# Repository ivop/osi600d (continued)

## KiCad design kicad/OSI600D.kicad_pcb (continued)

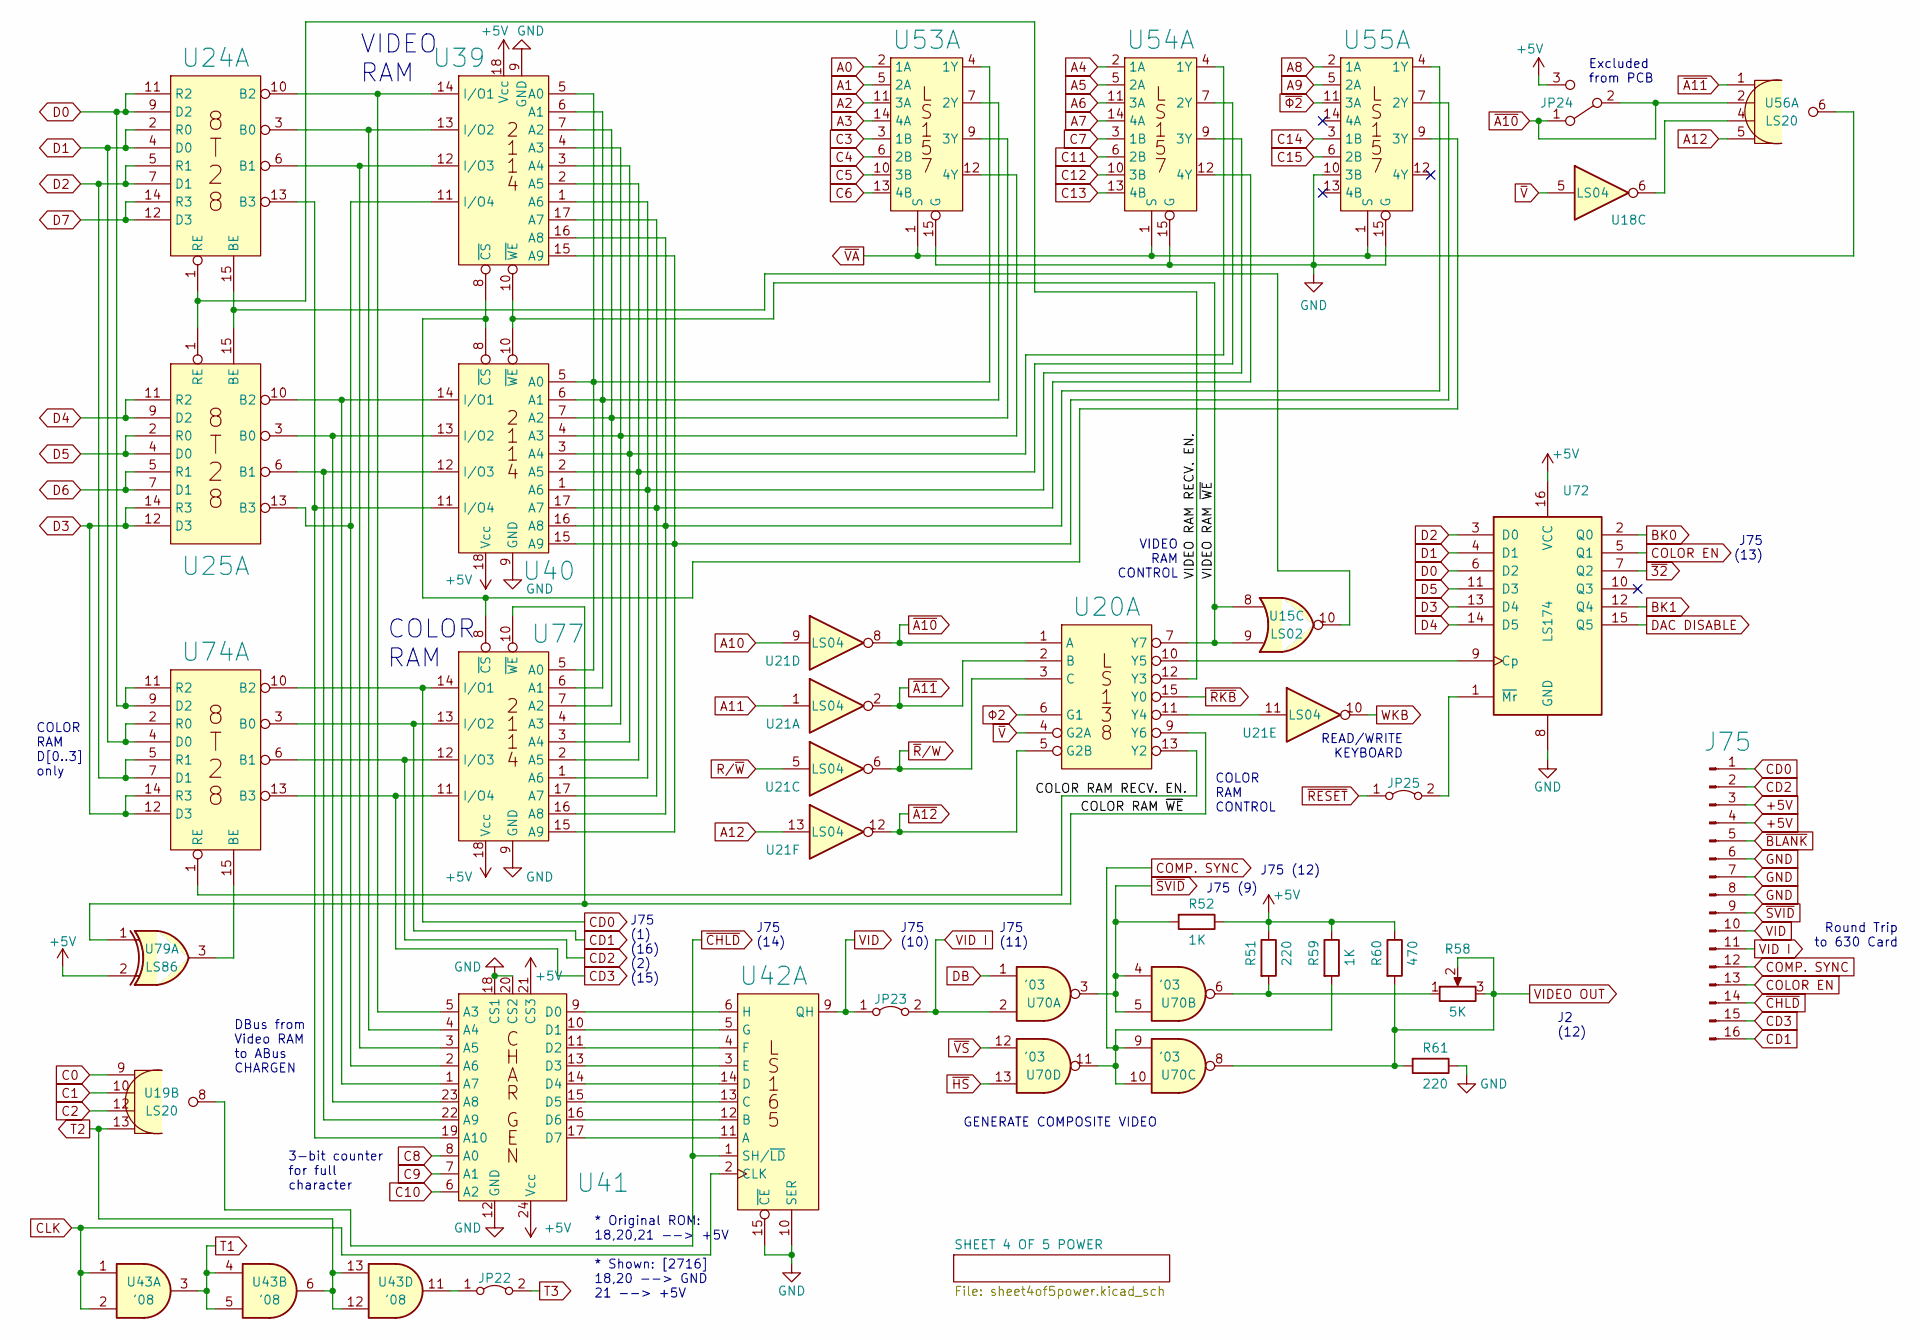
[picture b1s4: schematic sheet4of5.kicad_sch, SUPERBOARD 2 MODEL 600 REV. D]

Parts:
J75: Conn_01x16_Male; DIP-16_W7.62mm_Socket_LongPads
JP22, JP23, JP25: Jumper_2_Bridged; Closed_PinHeader_1x02_P2.54mm_Vertical
JP24: JUMPER; PinHeader_1x03_P2.54mm_Vertical
R51, R61: 220; R_Axial_DIN0207_L6.3mm_D2.5mm_P2.54mm_Vertical
R52, R59: 1K; R_Axial_DIN0207_L6.3mm_D2.5mm_P2.54mm_Vertical
R58: 5K; Potentiometer_Bourns_3296W_Vertical
R60: 470; R_Axial_DIN0207_L6.3mm_D2.5mm_P2.54mm_Vertical
U15: LS02; DIP-14_W7.62mm_Socket_LongPads
U18, U21: LS04; DIP-14_W7.62mm_Socket_LongPads
U19, U56: LS20; DIP-14_W7.62mm_Socket_LongPads
U20: LS138; DIP-16_W7.62mm_Socket_LongPads
U24, U25, U74: 8T28; DIP-16_W7.62mm_Socket_LongPads
U39: 2114 CS BOTTOM COMPACT; DIP-18_W7.62mm_Socket_LongPads
U40, U77: 2114 CS TOP COMPACT; DIP-18_W7.62mm_Socket_LongPads
U41: CHARGEN; DIP-24_W15.24mm_Socket_LongPads
U42: LS165; DIP-16_W7.62mm_Socket_LongPads
U43: '08; DIP-14_W7.62mm_Socket_LongPads
U53, U54, U55: LS157; DIP-16_W7.62mm_Socket_LongPads
U70: '03; DIP-14_W7.62mm_Socket_LongPads
U72: LS174; DIP-16_W7.62mm_Socket_LongPads
U79: LS86; DIP-14_W7.62mm_Socket_LongPads

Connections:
+5V: J75.3, J75.4, JP24.3, R51.1, R52.1, R59.1, R60.1, U39.18 (Vcc), U40.18 (Vcc), U41.21 (CS3), U41.24 (Vcc), U72.16 (VCC), U77.18 (Vcc), U79.2; also elsewhere on the board
/SHEET 4 OF 5/COLOR RAM RECV. EN.: U20.13 (Y2), U74.1 (RE)
/SHEET 4 OF 5/COLOR RAM ~WE: U20.9 (Y6), U77.10 (~WE), U79.1
/SHEET 4 OF 5/VIDEO RAM RECV. EN.: U20.12 (Y3), U24.1 (RE), U25.1 (RE)
/SHEET 4 OF 5/VIDEO RAM ~WE: U15.8, U15.9, U20.7 (Y7), U39.10 (~WE), U40.10 (~WE)
A0: U53.2 (1A); also elsewhere on the board
A1: U53.5 (2A); also elsewhere on the board
A2: U53.11 (3A); also elsewhere on the board
A3: U53.14 (4A); also elsewhere on the board
A4: U54.2 (1A); also elsewhere on the board
A5: U54.5 (2A); also elsewhere on the board
A6: U54.11 (3A); also elsewhere on the board
A7: U54.14 (4A); also elsewhere on the board
A8: U55.2 (1A); also elsewhere on the board
A9: U55.5 (2A); also elsewhere on the board
A10: U21.9; also elsewhere on the board
A11: U21.1; also elsewhere on the board
A12: U21.13, U56.5 (1D); also elsewhere on the board
BK0: U72.2 (Q0); also elsewhere on the board
BK1: U72.12 (Q4); also elsewhere on the board
C0: U19.9 (2A); also elsewhere on the board
C1: U19.10 (2B); also elsewhere on the board
C2: U19.12 (2C); also elsewhere on the board
C3: U53.3 (1B); also elsewhere on the board
C4: U53.6 (2B); also elsewhere on the board
C5: U53.10 (3B); also elsewhere on the board
C6: U53.13 (4B); also elsewhere on the board
C7: U54.3 (1B); also elsewhere on the board
C8: U41.8 (A0); also elsewhere on the board
C9: U41.7 (A1); also elsewhere on the board
C10: U41.6 (A2); also elsewhere on the board
C11: U54.6 (2B); also elsewhere on the board
C12: U54.10 (3B); also elsewhere on the board
C13: U54.13 (4B); also elsewhere on the board
C14: U55.3 (1B); also elsewhere on the board
C15: U55.6 (2B); also elsewhere on the board
CD0: J75.1, U74.10 (B2), U77.14 (I/O1)
CD1: J75.16, U74.3 (B0), U77.13 (I/O2)
CD2: J75.2, U74.6 (B1), U77.12 (I/O3)
CD3: J75.15, U74.13 (B3), U77.11 (I/O4)
CLK: U42.2 (CLK), U43.1, U43.2; also elsewhere on the board
COLOR EN: J75.13, U72.5 (Q1)
COMP. SYNC: J75.12, R59.2, U70.9, U70.10, U70.11
D0: U24.9 (D2), U24.11 (R2), U72.6 (D2), U74.9 (D2), U74.11 (R2); also elsewhere on the board
D1: U24.2 (R0), U24.4 (D0), U72.4 (D1), U74.2 (R0), U74.4 (D0); also elsewhere on the board
D2: U24.5 (R1), U24.7 (D1), U72.3 (D0), U74.5 (R1), U74.7 (D1); also elsewhere on the board
D3: U25.12 (D3), U25.14 (R3), U72.13 (D4), U74.12 (D3), U74.14 (R3); also elsewhere on the board
D4: U25.9 (D2), U25.11 (R2), U72.14 (D5); also elsewhere on the board
D5: U25.2 (R0), U25.4 (D0), U72.11 (D3); also elsewhere on the board
D6: U25.5 (R1), U25.7 (D1); also elsewhere on the board
D7: U24.12 (D3), U24.14 (R3); also elsewhere on the board
DAC DISABLE: U72.15 (Q5); also elsewhere on the board
DB: U70.1; also elsewhere on the board
GND: J75.6, J75.7, J75.8, R61.1, U39.9 (GND), U40.9 (GND), U41.12 (GND), U41.18 (CS1), U41.20 (CS2), U42.10 (SER), U42.15 (~CE), U53.15 (G), U54.15 (G), U55.10 (3B), U55.15 (G), U72.8 (GND), U77.9 (GND); also elsewhere on the board
unnamed: JP22.1 (A), U43.11
unnamed: JP25.2 (B), U72.1 (~Mr)
unnamed: R51.2, R58.1, U70.6
unnamed: U15.10, U24.15 (BE), U25.15 (BE)
unnamed: U18.6, U56.4 (1C)
unnamed: U20.10 (Y5), U72.9 (Cp)
unnamed: U20.11 (Y4), U21.11
unnamed: U24.3 (B0), U39.13 (I/O2), U41.4 (A4)
unnamed: U24.6 (B1), U39.12 (I/O3), U41.3 (A5)
unnamed: U24.10 (B2), U39.14 (I/O1), U41.5 (A3)
unnamed: U24.13 (B3), U40.11 (I/O4), U41.19 (A10)
unnamed: U25.3 (B0), U40.13 (I/O2), U41.23 (A8)
unnamed: U25.6 (B1), U40.12 (I/O3), U41.22 (A9)
unnamed: U25.10 (B2), U40.14 (I/O1), U41.1 (A7)
unnamed: U25.13 (B3), U39.11 (I/O4), U41.2 (A6)
unnamed: U39.1 (A6), U40.1 (A6), U54.9 (3Y), U77.1 (A6)
unnamed: U39.2 (A5), U40.2 (A5), U54.7 (2Y), U77.2 (A5)
unnamed: U39.3 (A4), U40.3 (A4), U54.4 (1Y), U77.3 (A4)
unnamed: U39.4 (A3), U40.4 (A3), U53.12 (4Y), U77.4 (A3)
unnamed: U39.5 (A0), U40.5 (A0), U53.4 (1Y), U77.5 (A0)
unnamed: U39.6 (A1), U40.6 (A1), U53.7 (2Y), U77.6 (A1)
unnamed: U39.7 (A2), U40.7 (A2), U53.9 (3Y), U77.7 (A2)
unnamed: U39.8 (~CS), U40.8 (~CS), U55.9 (3Y), U77.8 (~CS)
unnamed: U39.15 (A9), U40.15 (A9), U55.7 (2Y), U77.15 (A9)
unnamed: U39.16 (A8), U40.16 (A8), U55.4 (1Y), U77.16 (A8)
unnamed: U39.17 (A7), U40.17 (A7), U54.12 (4Y), U77.17 (A7)
unnamed: U41.9 (D0), U42.6 (H)
unnamed: U41.10 (D1), U42.5 (G)
unnamed: U41.11 (D2), U42.4 (F)
unnamed: U41.13 (D3), U42.3 (E)
unnamed: U41.14 (D4), U42.14 (D)
unnamed: U41.15 (D5), U42.13 (C)
unnamed: U41.16 (D6), U42.12 (B)
unnamed: U41.17 (D7), U42.11 (A)
unnamed: U74.15 (BE), U79.3
R/~W: U21.5; also elsewhere on the board
T1: U43.3, U43.4, U43.5
T2: U19.13 (2D), U43.6, U43.12, U43.13
T3: JP22.2 (B); also elsewhere on the board
VID: J75.10, JP23.1 (A), U42.9 (QH)
VID I: J75.11, JP23.2 (B), U70.2
VIDEO OUT: R58.2, R58.3, R60.2, R61.2, U70.8; also elsewhere on the board
WKB: U21.10; also elsewhere on the board
~32: U72.7 (Q2); also elsewhere on the board
~A10: JP24.1, JP24.2, U20.1 (A), U21.8, U56.2 (1B); also elsewhere on the board
~A11: U20.2 (B), U21.2, U56.1 (1A); also elsewhere on the board
~A12: U20.5 (G2B), U21.12; also elsewhere on the board
~BLANK: J75.5; also elsewhere on the board
~CHLD: J75.14, U19.8 (2Y), U42.1 (SH/~LD)
~HS: U70.13; also elsewhere on the board
~RESET: JP25.1 (A); also elsewhere on the board
~RKB: U20.15 (Y0); also elsewhere on the board
~R/W: U20.3 (C), U21.6; also elsewhere on the board
~SVID: J75.9, R52.2, U70.3, U70.4, U70.5
~VA: U53.1 (S), U54.1 (S), U55.1 (S), U56.6 (1Y); also elsewhere on the board
~VS: U70.12; also elsewhere on the board
~V: U18.5, U20.4 (G2A); also elsewhere on the board
~Φ2: U55.11 (3A); also elsewhere on the board
Φ2: U20.6 (G1); also elsewhere on the board

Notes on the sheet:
VIDEO RAM
Excluded from PCB
COLOR RAM
* Original ROM: 18,20,21 --> +5V * Shown: [2716] 18,20 --> GND 21 --> +5V
J75 (10)
READ/WRITE KEYBOARD
J75 (9)
J75 (14)
J2 (12)
GENERATE COMPOSITE VIDEO
J75 (13)
J75 (11)
3-bit counter for full character
J75 (1) (16) (2) (15)
Round Trip to 630 Card
COLOR RAM D[0..3] only
VIDEO RAM CONTROL
J75 (12)
DBus from Video RAM to ABus CHARGEN
COLOR RAM CONTROL

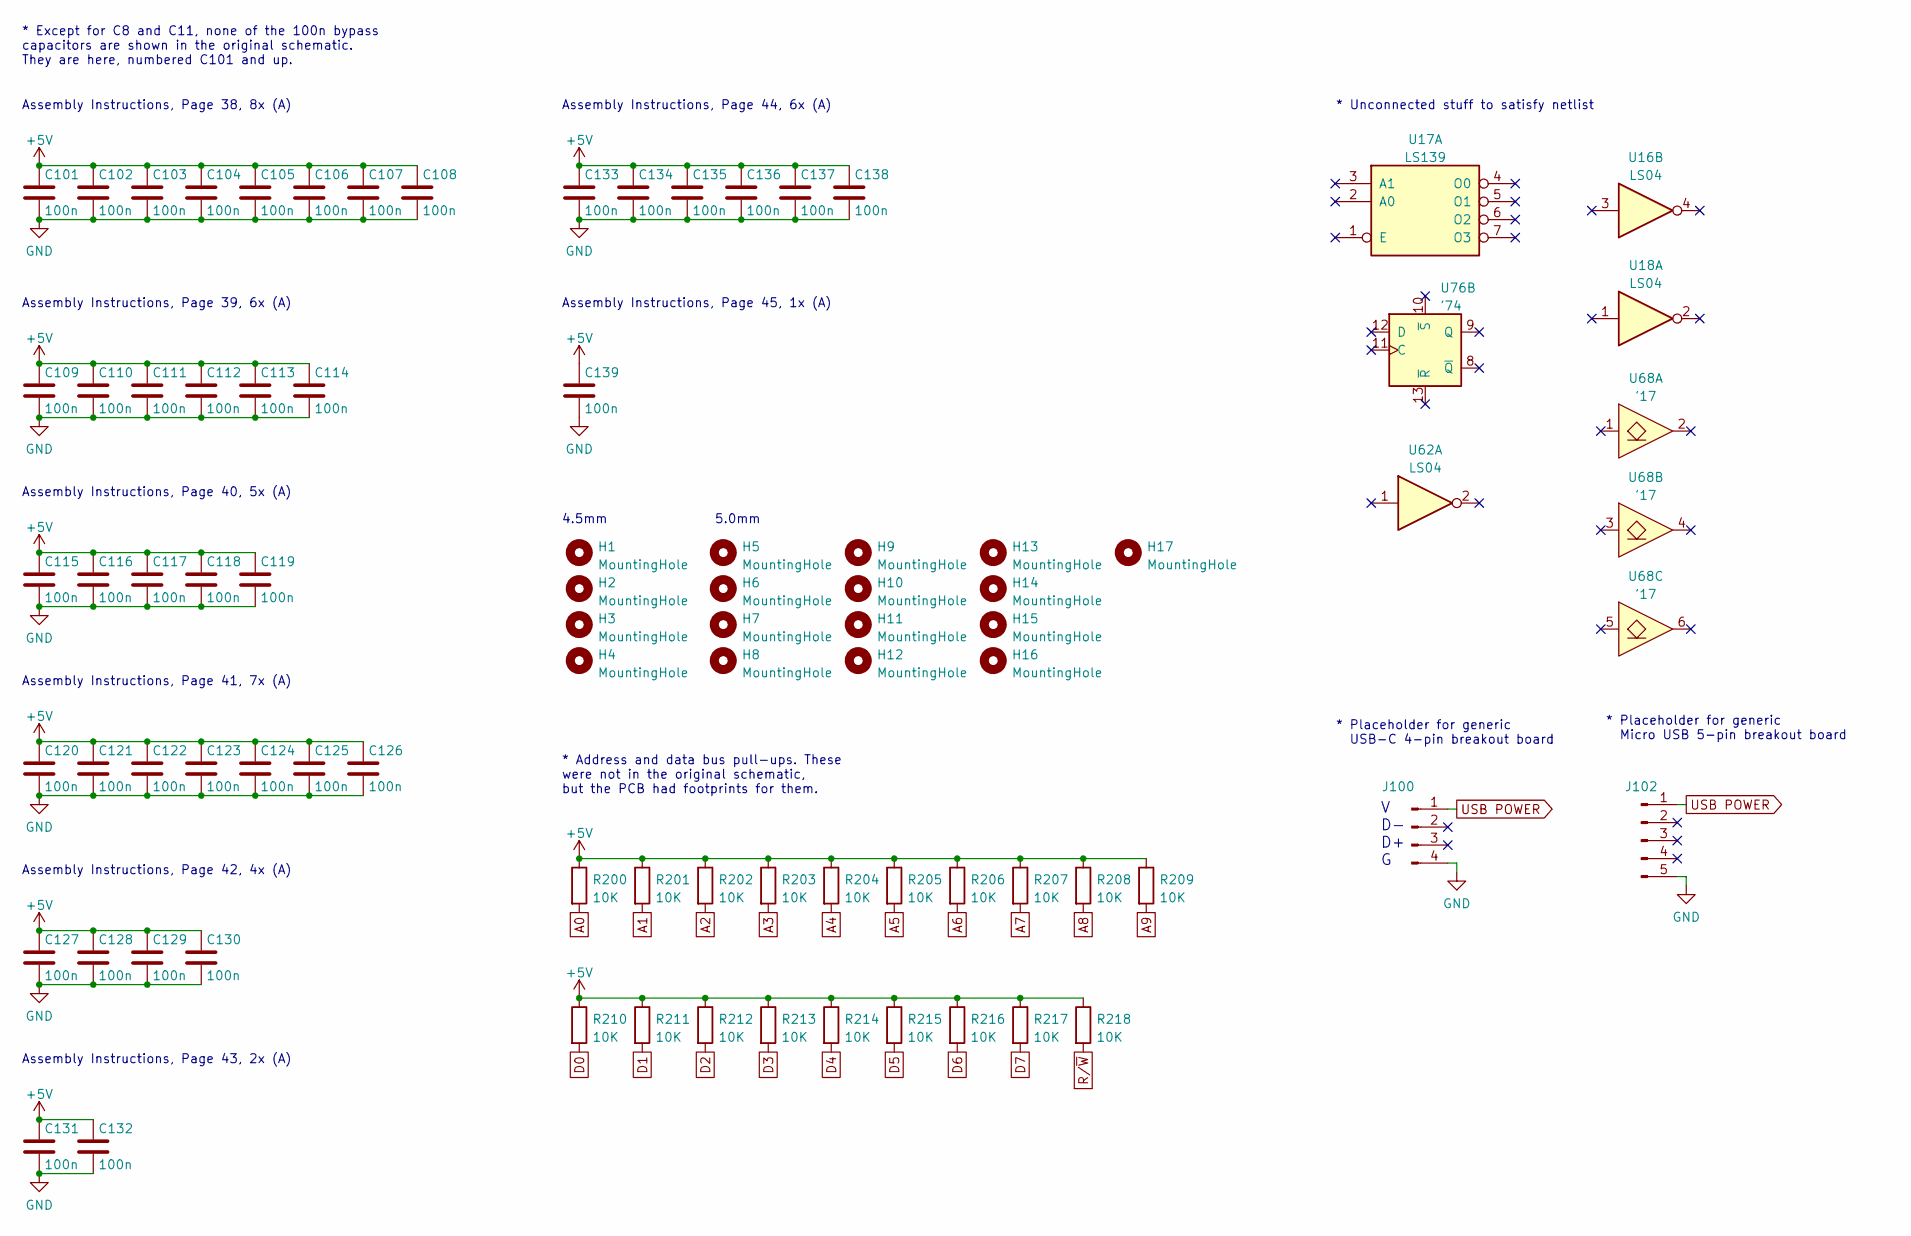
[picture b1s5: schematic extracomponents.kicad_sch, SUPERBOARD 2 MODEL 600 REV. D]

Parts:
C101, C102, C103, C104, C105, C106, C107, C108, C109, C110, C111, C112, C113, C114, C115, C116, C117, C118, C119, C120, C121, C122, C123, C124, C125, C126, C127, C128, C129, C130, C131, C132, C133, C134, C135, C136, C137, C138, C139: 100n; C_Disc_D7.5mm_W2.5mm_P7.50mm
H1, H2, H3, H4: MountingHole; MountingHole_4.5mm
H5, H6, H7, H8, H9, H10, H11, H12, H13, H14, H15, H16, H17: MountingHole; MountingHole_5mm
J100: USB; PinHeader_1x04_P2.54mm_Vertical
J102: USB; PinHeader_1x05_P2.54mm_Vertical
R200, R201, R202, R203, R204, R205, R206, R207, R208, R209, R210, R211, R212, R213, R214, R215, R216, R217, R218: 10K; R_Axial_DIN0207_L6.3mm_D2.5mm_P2.54mm_Vertical
U16, U18, U62: LS04; DIP-14_W7.62mm_Socket_LongPads
U17: LS139; DIP-16_W7.62mm_Socket_LongPads
U68: '17; DIP-14_W7.62mm_Socket_LongPads
U76: '74; DIP-14_W7.62mm_Socket_LongPads

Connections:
+5V: C101.1, C102.1, C103.1, C104.1, C105.1, C106.1, C107.1, C108.1, C109.1, C110.1, C111.1, C112.1, C113.1, C114.1, C115.1, C116.1, C117.1, C118.1, C119.1, C120.1, C121.1, C122.1, C123.1, C124.1, C125.1, C126.1, C127.1, C128.1, C129.1, C130.1, C131.1, C132.1, C133.1, C134.1, C135.1, C136.1, C137.1, C138.1, C139.1, R200.1, R201.1, R202.1, R203.1, R204.1, R205.1, R206.1, R207.1, R208.1, R209.1, R210.1, R211.1, R212.1, R213.1, R214.1, R215.1, R216.1, R217.1, R218.1; also elsewhere on the board
A0: R200.2; also elsewhere on the board
A1: R201.2; also elsewhere on the board
A2: R202.2; also elsewhere on the board
A3: R203.2; also elsewhere on the board
A4: R204.2; also elsewhere on the board
A5: R205.2; also elsewhere on the board
A6: R206.2; also elsewhere on the board
A7: R207.2; also elsewhere on the board
A8: R208.2; also elsewhere on the board
A9: R209.2; also elsewhere on the board
D0: R210.2; also elsewhere on the board
D1: R211.2; also elsewhere on the board
D2: R212.2; also elsewhere on the board
D3: R213.2; also elsewhere on the board
D4: R214.2; also elsewhere on the board
D5: R215.2; also elsewhere on the board
D6: R216.2; also elsewhere on the board
D7: R217.2; also elsewhere on the board
GND: C101.2, C102.2, C103.2, C104.2, C105.2, C106.2, C107.2, C108.2, C109.2, C110.2, C111.2, C112.2, C113.2, C114.2, C115.2, C116.2, C117.2, C118.2, C119.2, C120.2, C121.2, C122.2, C123.2, C124.2, C125.2, C126.2, C127.2, C128.2, C129.2, C130.2, C131.2, C132.2, C133.2, C134.2, C135.2, C136.2, C137.2, C138.2, C139.2, J100.4, J102.5; also elsewhere on the board
R/~W: R218.2; also elsewhere on the board
USB POWER: J100.1, J102.1; also elsewhere on the board

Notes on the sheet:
* Placeholder for generic USB-C 4-pin breakout board
Assembly Instructions, Page 40, 5x (A)
* Placeholder for generic Micro USB 5-pin breakout board
Assembly Instructions, Page 42, 4x (A)
V D- D+ G
* Unconnected stuff to satisfy netlist
Assembly Instructions, Page 45, 1x (A)
Assembly Instructions, Page 44, 6x (A)
4.5mm
* Address and data bus pull-ups. These were not in the original schematic, but the PCB had footprints for them.
Assembly Instructions, Page 39, 6x (A)
5.0mm
Assembly Instructions, Page 38, 8x (A)
* Except for C8 and C11, none of the 100n bypass capacitors are shown in the original schematic. They are here, numbered C101 and up.
Assembly Instructions, Page 41, 7x (A)
Assembly Instructions, Page 43, 2x (A)

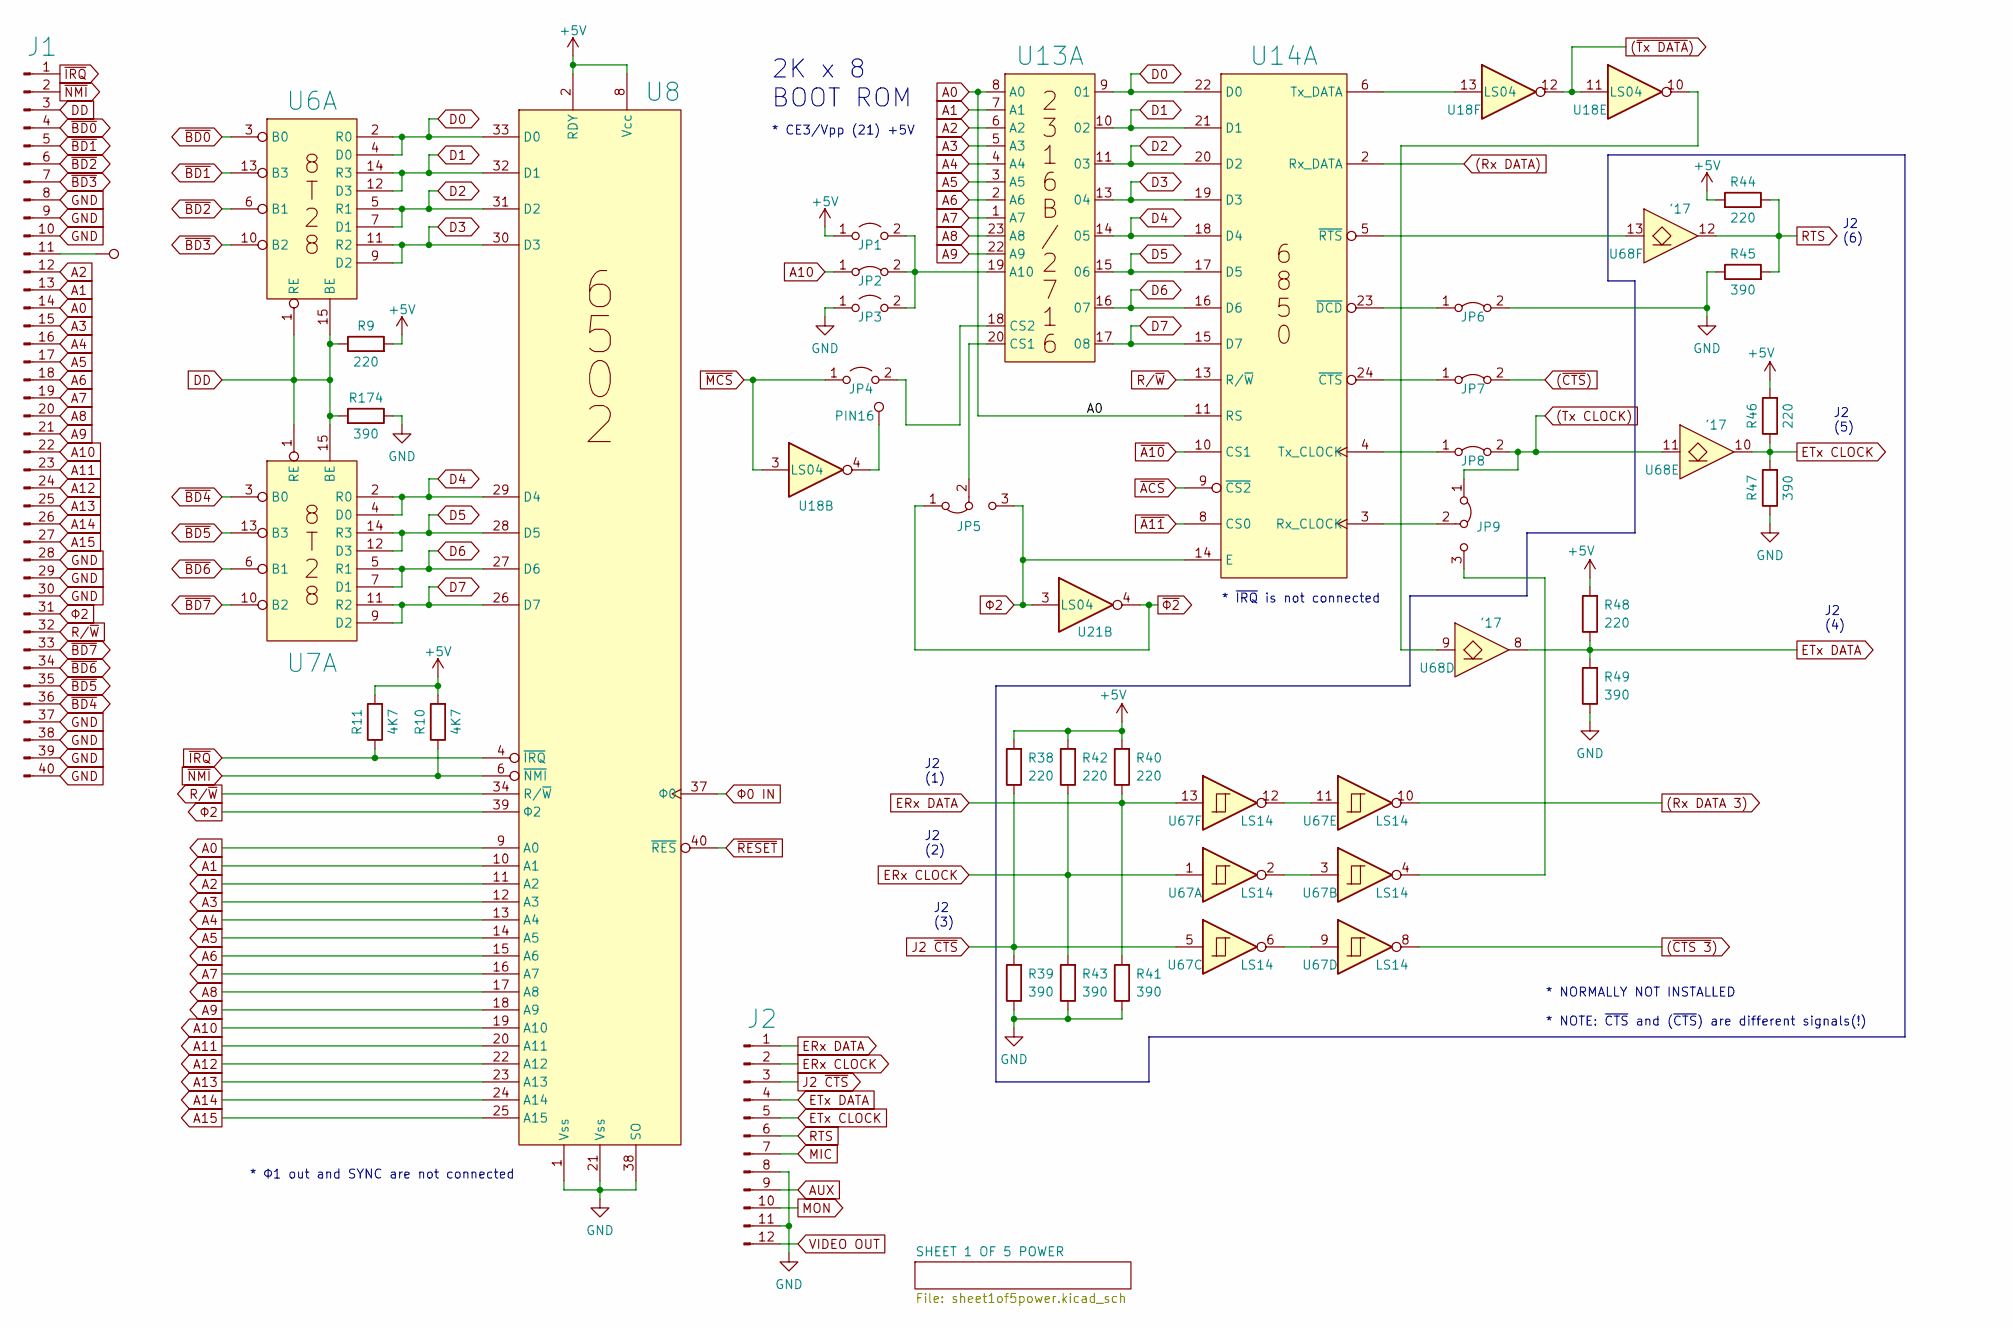
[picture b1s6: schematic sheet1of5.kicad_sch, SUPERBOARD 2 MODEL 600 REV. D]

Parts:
J1: Conn_01x40_Male; DIP-40_W15.24mm_Socket_LongPads
J2: Conn_01x12_Male; Molex_KK-396_A-41791-0012_1x12_P3.96mm_Vertical
JP1, JP3, JP4: Jumper_2_Open; PinHeader_1x02_P2.54mm_Vertical
JP2, JP6, JP7, JP8: Jumper_2_Bridged; Closed_PinHeader_1x02_P2.54mm_Vertical
JP5, JP9: Jumper_3_Bridged12; Closed 1-2 PinHeader_1x03_P2.54mm_Vertical
PIN15, PIN16: JUMPER_PIN; PinHeader_1x01_P2.54mm_Vertical
R9, R38, R40, R42, R44, R46, R48: 220; R_Axial_DIN0207_L6.3mm_D2.5mm_P2.54mm_Vertical
R10, R11: 4K7; R_Axial_DIN0207_L6.3mm_D2.5mm_P2.54mm_Vertical
R39, R41, R43, R45, R47, R49, R174: 390; R_Axial_DIN0207_L6.3mm_D2.5mm_P2.54mm_Vertical
U6, U7: 8T28; DIP-16_W7.62mm_Socket_LongPads
U8: 6502; DIP-40_W15.24mm_Socket_LongPads
U13: 2316B/2716; DIP-24_W15.24mm_Socket_LongPads
U14: 6850; DIP-24_W15.24mm_Socket_LongPads
U18, U21: LS04; DIP-14_W7.62mm_Socket_LongPads
U67: LS14; DIP-14_W7.62mm_Socket_LongPads
U68: '17; DIP-14_W7.62mm_Socket_LongPads

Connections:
(Rx DATA 3): U67.10; also elsewhere on the board
(Rx DATA): U14.2 (Rx_DATA); also elsewhere on the board
(Tx CLOCK): JP8.2 (B), JP9.1 (A), U68.11 (5A); also elsewhere on the board
(~CTS 3): U67.8; also elsewhere on the board
(~CTS): JP7.2 (B); also elsewhere on the board
(~Tx DATA): U18.11, U18.12; also elsewhere on the board
+5V: JP1.1 (A), R9.2, R10.2, R11.2, R38.2, R40.2, R42.2, R44.2, R46.2, R48.2, U8.2 (RDY), U8.8 (Vcc); also elsewhere on the board
A0: J1.14, U8.9 (A0), U13.8 (A0), U14.11 (RS); also elsewhere on the board
A1: J1.13, U8.10 (A1), U13.7 (A1); also elsewhere on the board
A2: J1.12, U8.11 (A2), U13.6 (A2); also elsewhere on the board
A3: J1.15, U8.12 (A3), U13.5 (A3); also elsewhere on the board
A4: J1.16, U8.13 (A4), U13.4 (A4); also elsewhere on the board
A5: J1.17, U8.14 (A5), U13.3 (A5); also elsewhere on the board
A6: J1.18, U8.15 (A6), U13.2 (A6); also elsewhere on the board
A7: J1.19, U8.16 (A7), U13.1 (A7); also elsewhere on the board
A8: J1.20, U8.17 (A8), U13.23 (A8); also elsewhere on the board
A9: J1.21, U8.18 (A9), U13.22 (A9); also elsewhere on the board
A10: J1.22, JP2.1 (A), U8.19 (A10); also elsewhere on the board
A11: J1.23, U8.20 (A11); also elsewhere on the board
A12: J1.24, U8.22 (A12); also elsewhere on the board
A13: J1.25, U8.23 (A13); also elsewhere on the board
A14: J1.26, U8.24 (A14); also elsewhere on the board
A15: J1.27, U8.25 (A15); also elsewhere on the board
AUX: J2.9; also elsewhere on the board
D0: U6.2 (R0), U6.4 (D0), U8.33 (D0), U13.9 (01), U14.22 (D0); also elsewhere on the board
D1: U6.12 (D3), U6.14 (R3), U8.32 (D1), U13.10 (02), U14.21 (D1); also elsewhere on the board
D2: U6.5 (R1), U6.7 (D1), U8.31 (D2), U13.11 (03), U14.20 (D2); also elsewhere on the board
D3: U6.9 (D2), U6.11 (R2), U8.30 (D3), U13.13 (04), U14.19 (D3); also elsewhere on the board
D4: U7.2 (R0), U7.4 (D0), U8.29 (D4), U13.14 (05), U14.18 (D4); also elsewhere on the board
D5: U7.12 (D3), U7.14 (R3), U8.28 (D5), U13.15 (06), U14.17 (D5); also elsewhere on the board
D6: U7.5 (R1), U7.7 (D1), U8.27 (D6), U13.16 (07), U14.16 (D6); also elsewhere on the board
D7: U7.9 (D2), U7.11 (R2), U8.26 (D7), U13.17 (08), U14.15 (D7); also elsewhere on the board
DD: J1.3, R9.1, R174.2, U6.1 (RE), U6.15 (BE), U7.1 (RE), U7.15 (BE)
ERx CLOCK: J2.2, R42.1, R43.2, U67.1
ERx DATA: J2.1, R40.1, R41.2, U67.13
ETx CLOCK: J2.5, R46.1, R47.2, U68.10 (5Y)
ETx DATA: J2.4, R48.1, R49.2, U68.8 (4Y)
GND: J1.8, J1.9, J1.10, J1.28, J1.29, J1.30, J1.37, J1.38, J1.39, J1.40, J2.8, J2.11, JP3.1 (A), JP6.2 (B), R39.1, R41.1, R43.1, R45.1, R47.1, R49.1, R174.1, U8.1 (Vss), U8.21 (Vss), U8.38 (SO); also elsewhere on the board
J2 ~CTS: J2.3, R38.1, R39.2, U67.5
MIC: J2.7; also elsewhere on the board
MON: J2.10; also elsewhere on the board
unnamed: J1.11, PIN15.1
unnamed: JP1.2 (B), JP2.2 (B), JP3.2 (B), U13.19 (A10)
unnamed: JP4.2 (B), U13.18 (CS2)
unnamed: JP5.2 (C), U13.20 (CS1)
unnamed: JP6.1 (A), U14.23 (~DCD)
unnamed: JP7.1 (A), U14.24 (~CTS)
unnamed: JP8.1 (A), U14.4 (Tx_CLOCK)
unnamed: JP9.2 (C), U14.3 (Rx_CLOCK)
unnamed: JP9.3 (B), U67.4
unnamed: PIN16.1, U18.4
unnamed: U14.5 (~RTS), U68.13 (6A)
unnamed: U14.6 (Tx_DATA), U18.13
unnamed: U18.10, U68.9 (4A)
unnamed: U67.2, U67.3
unnamed: U67.6, U67.9
unnamed: U67.11, U67.12
RTS: J2.6, R44.1, R45.2, U68.12 (6Y)
R/~W: J1.32, U8.34 (R/~W), U14.13 (R/~W); also elsewhere on the board
VIDEO OUT: J2.12; also elsewhere on the board
~A10: U14.10 (CS1); also elsewhere on the board
~A11: U14.8 (CS0); also elsewhere on the board
~ACS: U14.9 (~CS2); also elsewhere on the board
~BD0: J1.4, U6.3 (B0)
~BD1: J1.5, U6.13 (B3)
~BD2: J1.6, U6.6 (B1)
~BD3: J1.7, U6.10 (B2)
~BD4: J1.36, U7.3 (B0)
~BD5: J1.35, U7.13 (B3)
~BD6: J1.34, U7.6 (B1)
~BD7: J1.33, U7.10 (B2)
~IRQ: J1.1, R11.1, U8.4 (~IRQ)
~MCS: JP4.1 (A), U18.3; also elsewhere on the board
~NMI: J1.2, R10.1, U8.6 (~NMI)
~RESET: U8.40 (~RES); also elsewhere on the board
~Φ2: JP5.1 (A), U21.4; also elsewhere on the board
Φ0 IN: U8.37 (Φ0); also elsewhere on the board
Φ2: J1.31, JP5.3 (B), U8.39 (Φ2), U14.14 (E), U21.3; also elsewhere on the board

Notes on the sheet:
J2 (2)
J2 (5)
J2 (1)
* NORMALLY NOT INSTALLED * NOTE: ~{CTS} and (~{CTS}) are different signals(!)
* Φ1 out and SYNC are not connected
2K x 8 BOOT ROM
J2 (6)
* ~{IRQ} is not connected
J2 (4)
* CE3/Vpp (21) +5V
J2 (3)

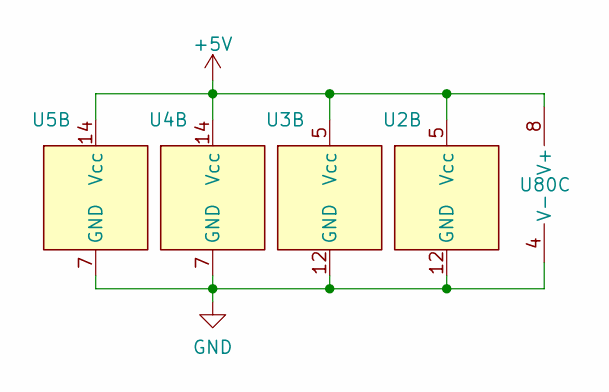
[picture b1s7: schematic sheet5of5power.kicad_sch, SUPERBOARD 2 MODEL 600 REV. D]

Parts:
U2, U3: LS75; DIP-16_W7.62mm_Socket_LongPads
U4, U5: LS125; DIP-14_W7.62mm_Socket_LongPads
U80: LM393; DIP-8_W7.62mm_Socket_LongPads

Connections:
+5V: U2.5 (Vcc), U3.5 (Vcc), U4.14 (Vcc), U5.14 (Vcc), U80.8 (V+); also elsewhere on the board
GND: U2.12 (GND), U3.12 (GND), U4.7 (GND), U5.7 (GND), U80.4 (V-); also elsewhere on the board

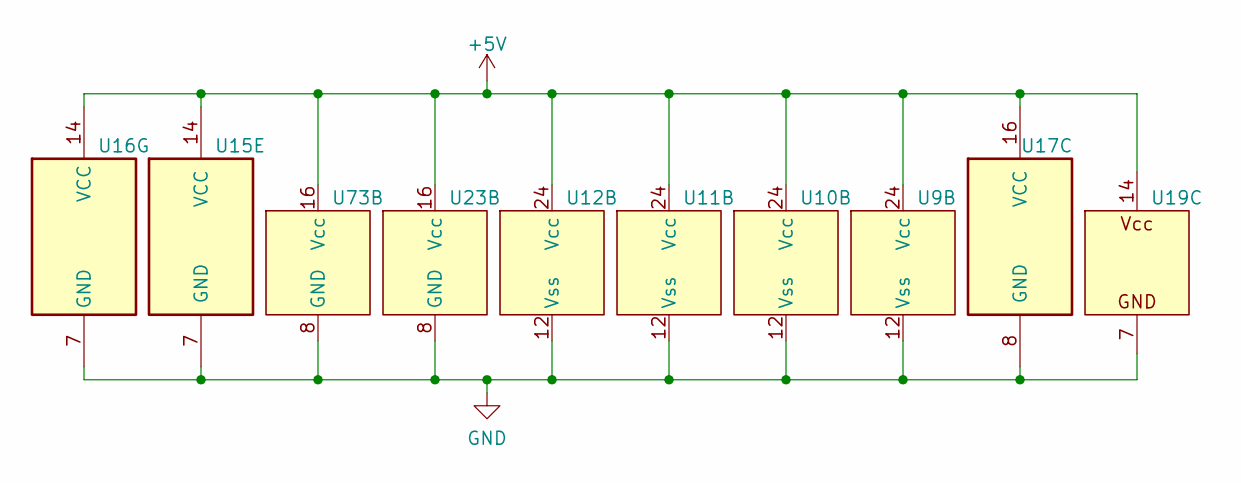
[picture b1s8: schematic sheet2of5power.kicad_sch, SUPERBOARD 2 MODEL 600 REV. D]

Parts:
U9: BASIC 1; DIP-24_W15.24mm_Socket_LongPads
U10: BASIC 2; DIP-24_W15.24mm_Socket_LongPads
U11: BASIC 3; DIP-24_W15.24mm_Socket_LongPads
U12: BASIC 4; DIP-24_W15.24mm_Socket_LongPads
U15: LS02; DIP-14_W7.62mm_Socket_LongPads
U16: LS04; DIP-14_W7.62mm_Socket_LongPads
U17: LS139; DIP-16_W7.62mm_Socket_LongPads
U19: LS20; DIP-14_W7.62mm_Socket_LongPads
U23, U73: LS138; DIP-16_W7.62mm_Socket_LongPads

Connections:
+5V: U9.24 (Vcc), U10.24 (Vcc), U11.24 (Vcc), U12.24 (Vcc), U15.14 (VCC), U16.14 (VCC), U17.16 (VCC), U19.14 (Vcc), U23.16 (Vcc), U73.16 (Vcc); also elsewhere on the board
GND: U9.12 (Vss), U10.12 (Vss), U11.12 (Vss), U12.12 (Vss), U15.7 (GND), U16.7 (GND), U17.8 (GND), U19.7 (GND), U23.8 (GND), U73.8 (GND); also elsewhere on the board

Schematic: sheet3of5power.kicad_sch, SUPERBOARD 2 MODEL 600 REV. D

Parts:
U18, U62: LS04; DIP-14_W7.62mm_Socket_LongPads
U30, U57, U59, U60, U61: LS163; DIP-16_W7.62mm_Socket_LongPads
U43: '08; DIP-14_W7.62mm_Socket_LongPads
U56: LS20; DIP-14_W7.62mm_Socket_LongPads
U58: '00; DIP-14_W7.62mm_Socket_LongPads
U63, U76: '74; DIP-14_W7.62mm_Socket_LongPads
U64: LS76; DIP-16_W7.62mm_Socket_LongPads
U65, U69: '123; DIP-16_W7.62mm_Socket_LongPads
U78: LS157; DIP-16_W7.62mm_Socket_LongPads
U79: LS86; DIP-14_W7.62mm_Socket_LongPads

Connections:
+5V: U18.14 (VCC), U30.16 (Vcc), U43.14 (VCC), U56.14 (Vcc), U57.16 (Vcc), U58.14 (VCC), U59.16 (Vcc), U60.16 (Vcc), U61.16 (Vcc), U62.14 (VCC), U63.14 (VCC), U64.5 (VCC), U65.16 (Vcc), U69.16 (Vcc), U76.14 (VCC), U78.16 (Vcc), U79.14 (VCC); also elsewhere on the board
GND: U18.7 (GND), U30.8 (GND), U43.7 (GND), U56.7 (GND), U57.8 (GND), U58.7 (GND), U59.8 (GND), U60.8 (GND), U61.8 (GND), U62.7 (GND), U63.7 (GND), U64.13 (GND), U65.8 (GND), U69.8 (GND), U76.7 (GND), U78.8 (GND), U79.7 (GND); also elsewhere on the board

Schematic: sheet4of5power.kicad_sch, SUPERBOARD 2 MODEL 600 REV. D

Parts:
U20: LS138; DIP-16_W7.62mm_Socket_LongPads
U21: LS04; DIP-14_W7.62mm_Socket_LongPads
U24, U25, U74: 8T28; DIP-16_W7.62mm_Socket_LongPads
U42: LS165; DIP-16_W7.62mm_Socket_LongPads
U53, U54, U55: LS157; DIP-16_W7.62mm_Socket_LongPads
U70: '03; DIP-14_W7.62mm_Socket_LongPads

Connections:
+5V: U20.16 (Vcc), U21.14 (VCC), U24.16 (Vcc), U25.16 (Vcc), U42.16 (Vcc), U53.16 (Vcc), U54.16 (Vcc), U55.16 (Vcc), U70.14 (VCC), U74.16 (Vcc); also elsewhere on the board
GND: U20.8 (GND), U21.7 (GND), U24.8 (GND), U25.8 (GND), U42.8 (GND), U53.8 (GND), U54.8 (GND), U55.8 (GND), U70.7 (GND), U74.8 (GND); also elsewhere on the board

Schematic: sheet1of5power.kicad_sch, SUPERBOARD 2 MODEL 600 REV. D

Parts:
U6, U7: 8T28; DIP-16_W7.62mm_Socket_LongPads
U13: 2316B/2716; DIP-24_W15.24mm_Socket_LongPads
U14: 6850; DIP-24_W15.24mm_Socket_LongPads
U67: LS14; DIP-14_W7.62mm_Socket_LongPads
U68: '17; DIP-14_W7.62mm_Socket_LongPads

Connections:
+5V: U6.16 (Vcc), U7.16 (Vcc), U13.21 (Vpp), U13.24 (Vcc), U14.12 (Vcc), U67.14 (VCC), U68.14 (Vcc); also elsewhere on the board
GND: U6.8 (GND), U7.8 (GND), U13.12 (Vss), U14.1 (Vss), U67.7 (GND), U68.7 (GND); also elsewhere on the board

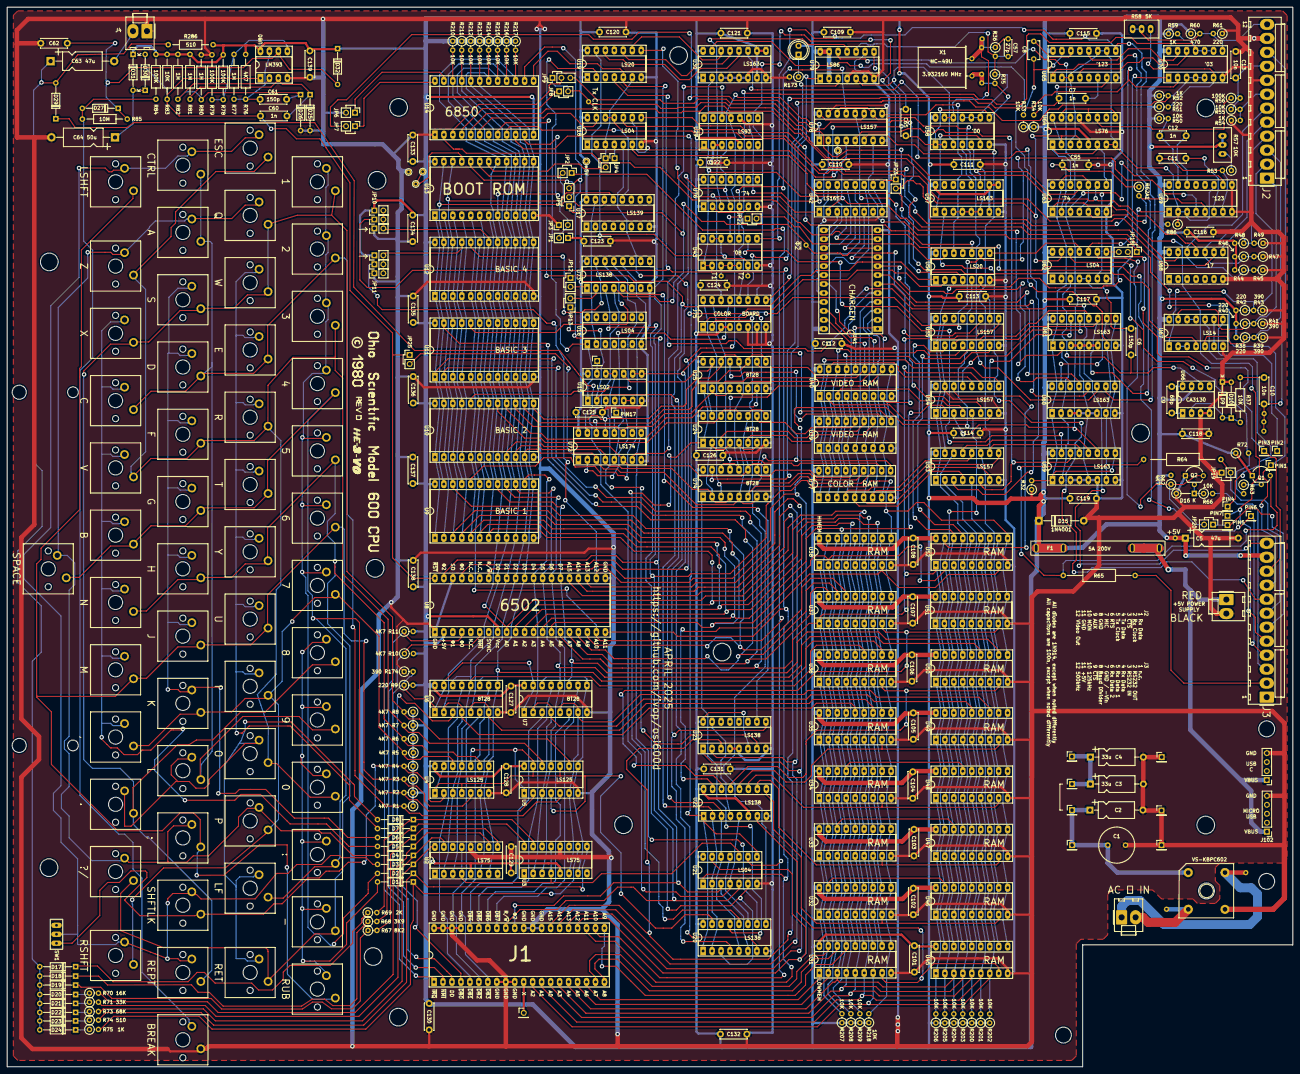
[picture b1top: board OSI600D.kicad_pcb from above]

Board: 2 copper layers, 364.0 x 300.0 mm, 385 parts (1 on the bottom side), 291 nets.

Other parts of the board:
nis-+5v-1: +5V
nis-C65-pad1: (no value)
nis-MON-pad: (no value)
nis-MON-pad-2: (no value)
nis-c65-pad1-2: (no value)
nis-phi2: ~{Φ2}
nis-rectifier-pad: (no value)

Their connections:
+5V: nis-+5v-1.1; also elsewhere on the board
MON: nis-C65-pad1.1, nis-MON-pad.1, nis-MON-pad-2.1; also elsewhere on the board
unnamed 106: nis-c65-pad1-2.1; also elsewhere on the board
unnamed 171: nis-rectifier-pad.1; also elsewhere on the board
~Φ2: nis-phi2.1; also elsewhere on the board

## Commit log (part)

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2025-04-29 First commit.
2025-05-08 Ignore stuff
2025-05-08 Switch J1 and J75 to pin headers.
2025-06-01 Fix number of 18-pin sockets
2025-07-19 Fix comments in schematic
2025-08-01 Add Micro USB Power component (5-pin breakout board)
2025-08-18 small update of silkscreen, remove sch-bak file(s)
